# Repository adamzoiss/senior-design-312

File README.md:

# Senior Design Project - Team 312

**Share Point Quick Link:** [Project SharePoint](https://fsu-my.sharepoint.com/personal/amw21i_fsu_edu/_layouts/15/Doc.aspx?sourcedoc={c8d6e6cb-04f5-4a5c-a4a4-ac70581ecfba}&action=edit&wd=target%28Class%20Handouts.one%7C43749e4e-c570-4688-8d40-703e8b013bf2%2FSenior%20Design%20Projects%7C01b6a98f-3880-41ca-834b-d67c770890d6%2F%29&wdorigin=NavigationUrl)

---

**Table of Contents**

> _The links are clickable and will take you to that section or subsection._

- [**Operation Manual**](#operation-manual)

  - [How to start the device](#how-to-start-the-device)
  - [How to operate](#how-to-operate)

- [**Project Description**](#project-description)

  - [Overall Processes](#overall-processes)
  - [Audio Processing and Transmission](#audio-processing-and-transmission-of-data)
  - [Encryption/Decryption Information](#how-the-encryption-and-decryption-works)
  - [Materials](#materials)

- [**RPI Setup**](#rpi-setup)

  - [Flashing an OS](#flashing-an-os)
  - [How to SSH to rpi](#how-to-ssh-to-rpi)
  - [Driver Installation](#driver-installation)

- [**Coding Environment**](#coding-environment)

  - [Running the Code](#running-the-code)

- [**Creating a daemon**](#creating-a-daemon)

- [**Using Git**](#using-git)

  - [Setting up Git](#setting-up-git)
  - [Git usage](#git-usage)

- [**Documenting Python Code**](#documenting-python-code)

  - [Code Documentation](#code-documentation)
  - [Type Hinting Guide](#type-hinting-guide)

- [**Contributors**](#contributors)

**Resources:**

[KiCad](https://www.kicad.org/) - The circuit schematic and PCB design files are in the kicad folder.

[PEP 8 – Style Guide for Python Code](https://peps.python.org/pep-0008/#introduction) - Guideline for how to code in Python

[Python Project/Package Template](https://github.com/pypa/sampleproject) - To better understand the structure of the project, a template for python projects/packages can be viewed as a reference.

[Raspberry Pi pinout information](https://pinout.xyz/) - Useful for setting up buttons, switches, RF chip, etc. via the GPIO pins.

[Git Information](https://git-scm.com/book/en/v2) - Information on how to use git.

---

## Operation Manual:

A Guide on how to operate the end project will be discussed in this section.

### How to start the device:

Ideally a daemon could be used to start the program when booted up but there was a bug where the audio volume would only be set to 50%. The surefire way to get the device up and running is to first log in to the RPI5s and then configure it and and run the program manually:

```
alsamixer
```

- Set the volume to 100%

```
cd git/senior-design-312
penva
python src/managers/interface_manager.py
```

- This will start the program and show the logs in the terminal window

### How to operate

On the OLED screen there are two menus, Settings, and mode.

The Settings menu allows for the user to select and deselect the encryption for the device.

```
PENC - Packet Encryption: This is enables or disables the transceivers on board AES encryption.

DENC - Data Encryption: THis enables or disables the software encryption of the data.
```

In the Mode menu, the user can select the desired type of encryption for the data.

```
AES - Standard AES-256 Encryption

RSA - (NOT IMPLEMENTED) RSA Encryption

HYB - Hybrid Encryption method: RSA encrypted AES key
```

---

Volume Control

- The rotary encoder is used to change the onboard volume, which can be seen at the top left of the screen.

Selection of menu options

- The center button is used to select options in the menu.

Returning to the main menu

- The left button is used to return to the home screen.

Navigation

- The up and down buttons navigate through the menus.

Transmitting

- Pressing and holding the right button will start the transmission of the voice data from one device to the other. Releasing it will stop the transmission. Like a walkie-talkie, only one transceiver can be transmitting at a time.

---

## Project Description:

The purpose of the project is to have a hardware implementation for voice encryption. The approach taken was to use two Raspberry Pi 5's that are capable of encrypting and decrypting audio streams using AES or RSA. The encrypted stream is then sent to another Raspberry Pi via the RFM69 915MHz transceiver where it is then decrypted and played back. The functionality is like that of a rudimentary military grade radio (encrypted walkie talkie).

### Overall Processes:

To record the audio a button on the device is pressed, starting a thread to handle recording the audio and then transmitting it as shown in the diagram. The receiving device, upon receiving the RF signal and start sequence will start playing back the audio.

```mermaid
%%{init: {'theme': 'default', 'themeVariables': { 'fontSize': '18px', 'fontFamily': 'arial', 'edgeLabelBackground':'#ffffff'}, 'flowchart': {'diagramPadding': 40, 'curve': 'linear'}} }%%
flowchart LR
    %% Increase arrow thickness
    linkStyle default stroke-width:3px;

    subgraph sender["Audio Transmission"]
        record["Record Audio"] --> process["Process Audio"]
        process --> encode["Encode Audio"]
        encode --> encrypt["Encrypt Data"]
        encrypt --> send["Send Data"]
    end

    subgraph receiver["Reception and Playback"]
        receive["Receive Data"] --> decrypt["Decrypt Data"]
        decrypt --> decode["Decode Audio"]
        decode --> playback["Playback Audio"]
    end

    sender <==> receiver

    classDef default fill:#f0f8ff,stroke:#333,stroke-width:2px;
    classDef process fill:#e6ffe6,stroke:#333,stroke-width:2px;
    classDef encrypt fill:#ffe6e6,stroke:#333,stroke-width:2px;

    class record,process,encode,encrypt,send,receive,decrypt,decode,playback process;
```

### Audio Processing and Transmission of data:

[Diagrams and information](docs/design_flow_diagrams.md)

### How the encryption and decryption works:

This design used AES 256, RSA 4096, and a hybrid method that is outlined below:
[AES-256](docs/aes.md)
[RSA-4096](docs/rsa.md)

### Materials:

- [Raspberry Pi 5](https://www.adafruit.com/product/5813)
- [RPI UPS](https://www.amazon.com/Geekworm-X1200-Raspberry-Shutdown-Detection/dp/B0CRYVC8C5/ref=sr_1_5?crid=3T93BCIOWTPNQ&dib=eyJ2IjoiMSJ9.DSS9mwB54EGjoH9xGkIHFd17faf9UodmdVZNEF_NOwU1_TtXE9s5ghDnBO93wSyNeB1lbRl8e1wEuyPHb3ZzxMwYsCVhmp-j85LuohlRSUfx-YZh10-CHeAW6Z2ln4s2YudasiG1aBX-cWL1VihQCH_vzZzjAtUG9teGnXM9BbOQCqw_GdSpZU175fsOAMTuqZAPb5n3mfgUwXqlgPdfhwnoqzu5ng3niiaieRxPhM2FF5Hz5nVOXCaIMCLdwqQHWaklxH1ObAC3PyNYaox4awEBOQx2zcOAy6-PPfX7jiT5Lc-Iv-FmTJBIp-wI4evsTNgZJfQ-FAyS--bPdEAYpfdK69StwQNbdMvML9t9LII.ysi9Ba5JT9anmJP7jrCq64x9GX5JekWu3_toRT-0F-U&dib_tag=se&keywords=rpi5+ups+geekworm&qid=1743437047&s=electronics&sprefix=rpi5+ups+geekworm%2Celectronics%2C111&sr=1-5)
- [ANO Directional Navigation](https://www.adafruit.com/product/5001)
- [RFM69HCW Transceiver](https://www.adafruit.com/product/3070)
- [Voice Bonnet](https://www.adafruit.com/product/4757)
- [OLED Display](https://www.amazon.com/dp/B0CHF7LHVT?ref=ppx_yo2ov_dt_b_fed_asin_title&th=1)
- [Speaker](https://www.adafruit.com/product/4227)

---

## RPI Setup:

### Flashing an OS:

1. Download the [Raspberry PI imager](https://www.raspberrypi.com/software/)

2. Select RPI 5 as device and Raspian 64-bit Lite as OS
   2.1 - For all the drivers for this project, a non desktop version must be used.

3. Customize settings before flashing

   - Name the device (ex. rpi5-312)
   - Set username (ex. team312)
   - Set password (ex. password)
   - Enable SSH in second tab
   - Finally flash the SD card with the OS

4. Plug SD card in, power on

---

### How to SSH to rpi:

_This step is optional_

Using powershell or terminal (must be on same network)

```bash
ssh [username]@[device name].local
```

- Follow steps to allow connection

- To make life simpler going forward, get the VS code extension _Remote Explorer_
  - Then follow steps to make a SSH connection in VS code.

---

### Driver Installation:

- This will update all the base packages and drivers for the Raspberry Pi.

  ```bash
  sudo apt update
  sudo apt -y upgrade
  sudo reboot
  ```

  - The following steps are for ease of installation of all the necessary packages/drivers for the RPI. Running the setup script will install all the packages as well as create a virtual python environment in the _senior-design-312_ directory.

  - This script also adds aliases to the .bashrc and exports the directory of the project to PYTHONPATH.

  ADDED ALIASES:

  - ptree - shows the tree of the directory, excludes some of the unimportant files.
  - penvca - Creates and activates a python virtual environment in _**.env**_
  - penva - Activates the python virtual environment.

  ```bash
  sudo apt install -y git
  mkdir git
  cd git
  git clone https://github.com/adamzoiss/senior-design-312.git
  cd senior-design-312
  cd setup_utils
  chmod +x setup.sh
  ./setup.sh
  ```

  - After the reboot, change the directory to _senior-design-312_ and run:

    ```bash
    penva
    ```

  All of the code should now be ready to run in the project.

---

## Coding Environment:

- When running the code ensure that the virtual environment is activated, if the setup script was run, in the project directory, run:
  ```bash
  penva
  ```

---

### Running the Code:

- Assuming the setup script was run to configure the RPI, ensure the virtual environment is activated (.env) to the left of your bash info, and run:

  ```bash
  python "path to python program"
  ```

- To run the tests and view the statistics, run:
  ```bash
  pytest
  ```

---

## Creating a daemon:

A daemon is a background process that runs continuously and independently of user interaction. It starts at boot (or when needed) and runs in the background, typically without a graphical interface. Daemons are often used for tasks like logging, networking, and running services (like web servers, audio managers, etc.). In the case of this project, a daemon is used to start the interface manager program on boot, and if it crashes, restarts the program.

- Creating a Systemd Service:
  ```bash
  sudo nano /etc/systemd/system/run-py-program.service
  ```
  > This should be pasted and modified to use the correct python path, program directory, and _pi_ username

```
[Unit]
Description=My Python Script Daemon
After=network.target sound.target
Wants=pulseaudio.service

[Service]
ExecStart=/home/pi/git/senior-design-312/.env/bin/python /home/pi/git/senior-design-312/src/managers/interface_manager.py
WorkingDirectory=/home/adamzoiss/git/senior-design-312
Environment="PYTHONPATH=/home/pi/git/senior-design-312"
User=pi
Group=pi
Restart=always
RestartSec=5
StandardOutput=append:/home/pi/git/senior-design-312/logs/system.log
StandardError=append:/home/pi/git/senior-design-312/logs/system.err

[Install]
WantedBy=multi-user.target
```

- Allow Systemd to use pulse audio:

  > By default, PulseAudio does not allow system services to access it. Run:

  ```
  sudo nano /etc/pulse/client.conf
  ```

  - At the end of the file, add:
    ```
    autospawn = yes
    ```
  - Then restart pulseaudio
    ```
    pulseaudio -k
    pulseaudio --start
    ```

- Enabling and staring the daemon:

  > To apply the changes made in the _.service_ file:

  ```
  sudo systemctl daemon-reload
  ```

  > To enable:

  ```
  sudo systemctl enable run-py-program.service
  ```

  > To start:

  ```
  sudo systemctl start run-py-program.service
  ```

  > View the status:

  ```
  sudo systemctl status run-py-program.service
  ```

  - More useful commands:
    ```
    sudo systemctl disable run-py-program.service
    sudo systemctl stop run-py-program.service
    sudo systemctl restart run-py-program.service
    ```

---

## Using Git:

Git is a distributed version control system designed to track changes in source code during software development. It allows multiple developers to collaborate on a project by managing code changes, maintaining a history of modifications, and enabling branching and merging workflows. Git ensures code integrity and simplifies collaboration by providing tools to resolve conflicts and review changes.

### Setting up Git:

- First set username and password via:

  ```bash
  git config --global user.name "github username"
  git config --global user.email "github email"
  ```

  - To verify they were set correctly:
    ```bash
    git config --global -l
    ```

  1. Make a github account (Make sure you set your username and email in global config)
  2. install _gh_ for github authentication
     ```bash
     sudo apt install gh
     gh auth login
     ```
  3. Follow steps and log in
  4. Verify with:
     ```bash
     gh auth status
     ```

---

### Git usage

- Always make edits in a `branch`, do not work directly on main. To see what branch is active:

  ```bash
  git branch
  ```

- To `checkout` an active branch with name _branchname_:

  ```bash
  git checkout branchname
  ```

- To create a new working branch:

  ```bash
  git checkout -b nameofbranch
  ```

- After making changes on a branch, save (`commit`) the changes by:

  ```bash
  git commit -a -m "brief description of what was done"
  ```

  - This saves the changes locally on your computer, to add (push the changes to github)
    ```bash
    git push origin branchname
    ```
    - Alternatively, If you want Git to automatically set upstream branches when pushing new local branches, you can enable:
      ```bash
      git config --global push.autoSetupRemote true
      ```
      This way, next time you create a new branch and push, Git will automatically set up the remote tracking branch. The command will now look like:
      ```bash
      git push
      ```

- Getting the most up to date code:
  - save changes that were done on your branch via a commit or stash
  - check out `main`
    ```bash
    git fetch
    ```
    ```bash
    git pull
    ```
  - the most up to date version of main is now what you see

---

## Documenting Python Code:

### Code Documentation

`numpy` style documentation is being used for this project.

**Example of a NumPy-style docstring:**

```python
import numpy as np

def compute_mean(arr):
    """
    Compute the mean of a NumPy array.

    Parameters
    ----------
    arr : numpy.ndarray
        Input array of numerical values.

    Returns
    -------
    float
        The mean (average) of the input array.

    Raises
    ------
    ValueError
        If the input is not a NumPy array.

    Examples
    --------
    >>> import numpy as np
    >>> arr = np.array([1, 2, 3, 4, 5])
    >>> compute_mean(arr)
    3.0
    """
    if not isinstance(arr, np.ndarray):
        raise ValueError("Input must be a NumPy array.")
    return arr.mean()
```

**Breakdown of the NumPy docstring format:**

- Short summary: The first line briefly describes what the function does.
- Parameters: List of arguments, types, and descriptions.
- Returns: Description of the return value and type.
- Raises: Expected exceptions that may be thrown.
- Examples: Demonstrates usage with `doctest`-style examples.

---

**Class with NumPy-style Docstrings**

This class represents a **Simple Linear Regression** model.

```python
import numpy as np

class SimpleLinearRegression:
    """
    A simple linear regression model using the least squares method.

    Attributes
    ----------
    coef_ : float
        The slope (coefficient) of the regression line.
    intercept_ : float
        The y-intercept of the regression line.

    Methods
    -------
    fit(X, y)
        Fits the model to the data.
    predict(X)
        Predicts values using the trained model.
    """

    def __init__(self):
        """
        Initializes the SimpleLinearRegression model with no trained parameters.
        """
        self.coef_ = None
        self.intercept_ = None

    def fit(self, X, y):
        """
        Fit the linear regression model to the given dataset.

        Parameters
        ----------
        X : numpy.ndarray
            Feature array of shape (n_samples,).
        y : numpy.ndarray
            Target array of shape (n_samples,).

        Raises
        ------
        ValueError
            If `X` and `y` have different lengths.

        Examples
        --------
        >>> import numpy as np
        >>> X = np.array([1, 2, 3, 4, 5])
        >>> y = np.array([2, 4, 6, 8, 10])
        >>> model = SimpleLinearRegression()
        >>> model.fit(X, y)
        """
        if len(X) != len(y):
            raise ValueError("X and y must have the same length.")

        X_mean = np.mean(X)
        y_mean = np.mean(y)

        num = np.sum((X - X_mean) * (y - y_mean))
        den = np.sum((X - X_mean) ** 2)

        self.coef_ = num / den
        self.intercept_ = y_mean - self.coef_ * X_mean

    def predict(self, X):
        """
        Predict the target values for given input data.

        Parameters
        ----------
        X : numpy.ndarray
            Feature array of shape (n_samples,).

        Returns
        -------
        numpy.ndarray
            Predicted values based on the trained model.

        Raises
        ------
        ValueError
            If the model has not been trained yet.

        Examples
        --------
        >>> import numpy as np
        >>> X = np.array([6, 7, 8])
        >>> model = SimpleLinearRegression()
        >>> model.fit(np.array([1, 2, 3, 4, 5]), np.array([2, 4, 6, 8, 10]))
        >>> model.predict(X)
        array([12., 14., 16.])
        """
        if self.coef_ is None or self.intercept_ is None:
            raise ValueError("Model is not trained. Call `fit` first.")

        return self.coef_ * X + self.intercept_
```

**NumPy Docstrings Benefits**

- Structured and readable: Clearly defines parameters, return values, and exceptions.
- Works with auto-documentation tools like Sphinx.
- Encourages best practices: Makes it easier to maintain and understand code.

---

### Type Hinting Guide:

1. Function Arguments & Return Types

   ```python
   def add(x: int, y: int) -> int:
       return x + y
   ```

   `x: int` and `y: int` specify that x and y should be integers.

   `-> int` means the function returns an integer.

2. Variable Annotations

   ```python
   name: str = "Alice"
   age: int = 25
   height: float = 5.9
   is_active: bool = True
   ```

3. Lists, Tuples, and Dictionaries

   Use `list`, `tuple`, and `dict` with generic types:

   ```python
   from typing import List, Tuple, Dict

   numbers: List[int] = [1, 2, 3, 4]
   point: Tuple[float, float] = (3.5, 7.2)
   person: Dict[str, int] = {"age": 30, "score": 95}
   ```

- `List[int]`: A list of integers.
- `Tuple[float, float]`: A tuple with two floats.
- `Dict[str, int]`: A dictionary with string keys and integer values.

4. Optional & Union Types

   **Optional Type (Allows `None`)**

   ```python
   from typing import Optional

   def get_user_name(user_id: int) -> Optional[str]:
       return "Alice" if user_id == 1 else None
   ```

   `Optional[str]` is equivalent to `Union[str, None]`.

   **Union (Multiple Types Allowed)**

   ```python
   from typing import Union

   def parse_value(value: Union[int, str]) -> str:
       return str(value)
   ```

   `Union[int, str]` means `value` can be an **int** or **str**.

5. Custom Classes as Types

   ```python
   class User:
       def __init__(self, name: str):
           self.name = name

   def greet(user: User) -> str:
       return f"Hello, {user.name}!"
   ```

   The function `greet` expects a `User` instance.

6. Callable (Hinting Functions)

   ```python
   from typing import Callable

   def execute(func: Callable[[int, int], int], x: int, y: int) -> int:
       return func(x, y)

   def multiply(a: int, b: int) -> int:
       return a * b

   result = execute(multiply, 3, 4)  # Returns 12
   ```

   `Callable[[int, int], int]` means a function that:

   - Takes two integeres.
   - Returns an integer.

7. Type Aliases (For Readability)

   ```python
   from typing import List

   Coordinates = List[Tuple[float, float]]  # Type alias

   route: Coordinates = [(10.0, 20.0), (30.5, 40.2)]
   ```

   Now, `Coordinates` can be used instead of `List[Tuple[float, float]]`.

8. Type Variables (For Generic Functions & Classes)

   _This is the same concept in C++ as `template <Typename T>`_

   ```python
   from typing import TypeVar, Generic

   T = TypeVar('T')  # Generic Type

   def repeat(value: T, times: int) -> List[T]:
       return [value] * times

   print(repeat("Hello", 3))  # ['Hello', 'Hello', 'Hello']
   ```

   Here:

   - `T` is a Type Variable that allows any type.
   - `repeat` works with any type, maintaining type safety.

9. TypedDict (For Struct-like Dictionaries)

   ```python
   from typing import TypedDict

   class UserDict(TypedDict):
       name: str
       age: int

   user: UserDict = {"name": "Alice", "age": 30}
   ```

   This ensures `user` has only the specified keys and types.

10. `Self` Type Hinting for Methods

    Introduced in Python 3.11, `Self` hints that a method returns an instance of its class.

    ```python
    from typing import Self

    class Animal:
        def set_name(self, name: str) -> Self:
            self.name = name
            return self  # Returns instance for method chaining

    dog = Animal().set_name("Buddy")
    ```

---

**Static Type Checking with `mypy`**

To enforce type checking, install mypy:

```bash
pip install mypy
```

Then run:

```bash
mypy my_script.py
```

This will flag type errors before runtime.

---

## Contributors:

Danielle Awoniyi : danielle1.awoniyi@famu.edu

Amira McKaige : amm21bc@fsu.edu

Amelia Wondracek : amw21i@fsu.edu

Travis Gabauer : tg21b@fsu.edu

Adam Zoiss : aez18@fsu.edu

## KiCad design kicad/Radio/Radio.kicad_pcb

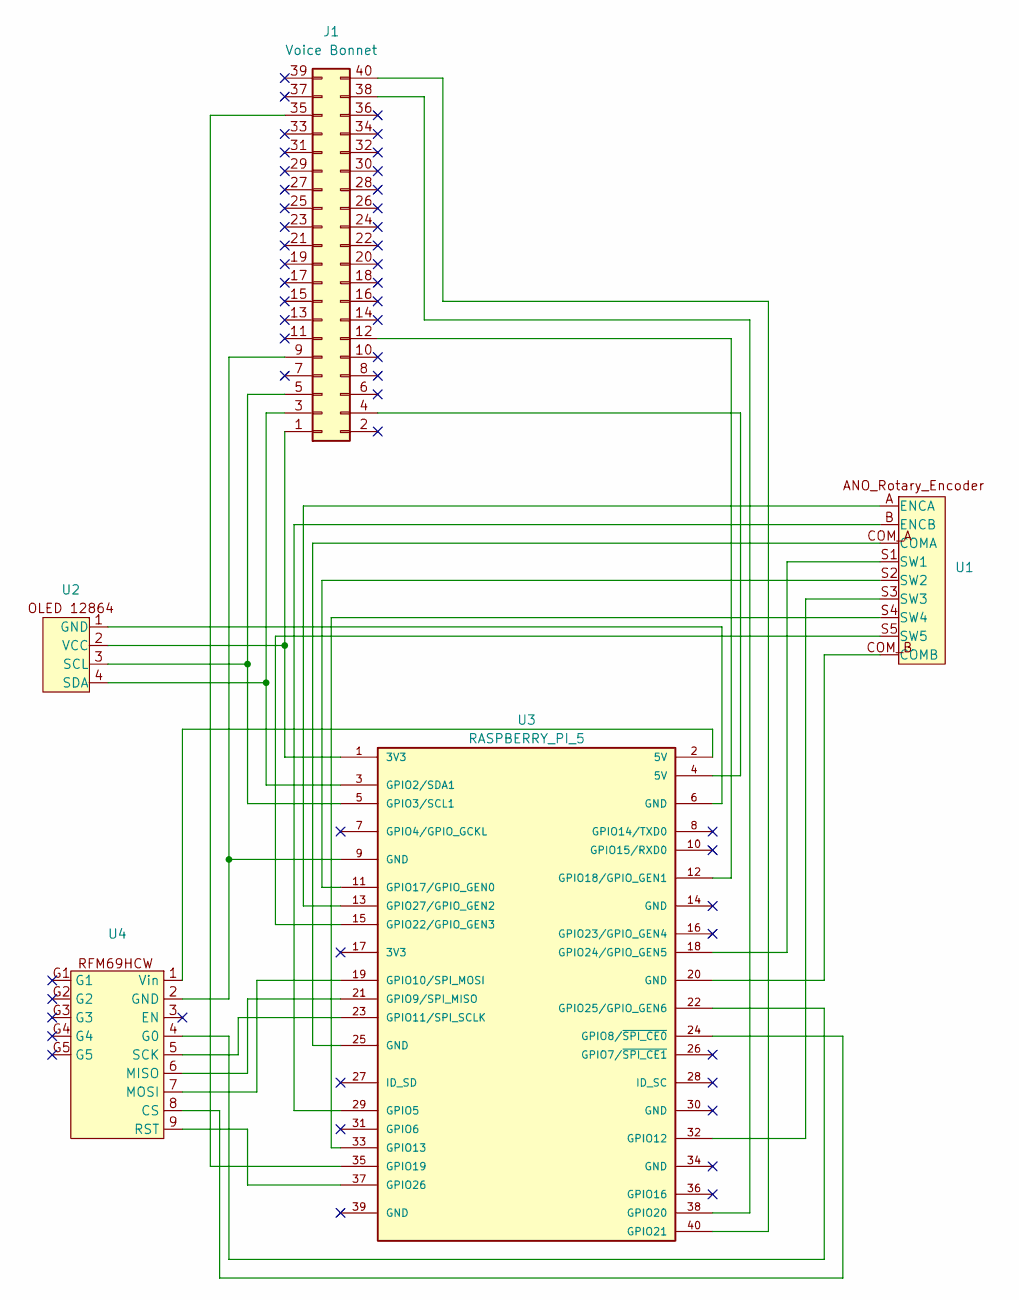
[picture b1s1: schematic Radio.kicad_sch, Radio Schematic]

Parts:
J1: Voice Bonnet; Voice_Bonnet
U1: ANO
U2: PinHeader_1x04_P2.54mm_Vertical
U3: RASPBERRY_PI_5; MODULE_RASPBERRY_PI_4B_4GB; PARTREV 4
U4: rfm69

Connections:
unnamed: J1.1, U2.2 (VCC), U3.1 (3V3)
unnamed: J1.3, U2.4 (SDA), U3.3 (GPIO2/SDA1)
unnamed: J1.4, U3.4 (5V)
unnamed: J1.5, U2.3 (SCL), U3.5 (GPIO3/SCL1)
unnamed: J1.9, U3.9 (GND), U4.2 (GND)
unnamed: J1.12, U3.12 (GPIO18/GPIO_GEN1)
unnamed: J1.35, U3.35 (GPIO19)
unnamed: J1.38, U3.38 (GPIO20)
unnamed: J1.40, U3.40 (GPIO21)
unnamed: U1.COM_A (COMA), U3.25 (GND)
unnamed: U1.COM_B (COMB), U3.20 (GND)
unnamed: U1.A (ENCA), U3.13 (GPIO27/GPIO_GEN2)
unnamed: U1.B (ENCB), U3.29 (GPIO5)
unnamed: U1.S1 (SW1), U3.18 (GPIO24/GPIO_GEN5)
unnamed: U1.S2 (SW2), U3.11 (GPIO17/GPIO_GEN0)
unnamed: U1.S3 (SW3), U3.32 (GPIO12)
unnamed: U1.S4 (SW4), U3.33 (GPIO13)
unnamed: U1.S5 (SW5), U3.15 (GPIO22/GPIO_GEN3)
unnamed: U2.1 (GND), U3.6 (GND)
unnamed: U3.24 (GPIO8/~SPI_CE0), U4.8 (CS)
unnamed: U3.21 (GPIO9/SPI_MISO), U4.6 (MISO)
unnamed: U3.19 (GPIO10/SPI_MOSI), U4.7 (MOSI)
unnamed: U3.23 (GPIO11/SPI_SCLK), U4.5 (SCK)
unnamed: U3.22 (GPIO25/GPIO_GEN6), U4.4 (G0)
unnamed: U3.37 (GPIO26), U4.9 (RST)
unnamed: U3.2 (5V), U4.1 (Vin)

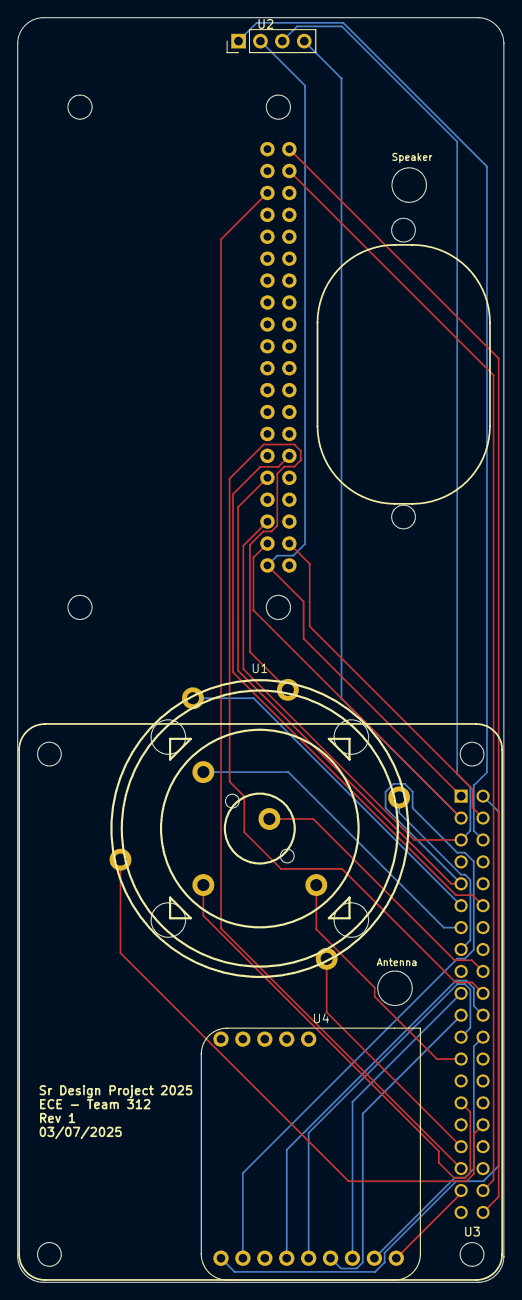
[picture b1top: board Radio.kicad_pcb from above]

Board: 2 copper layers, 56.4 x 146.6 mm, 5 parts (1 on the bottom side), 26 nets.

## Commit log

2025-01-14 Updated readme file
2025-01-14 Updated readme file part 2
2025-01-27 Create file structure
2025-01-27 added main file
2025-01-27 Working audio and encryption
2025-01-27 Updated encyption/decryption and audio driver
2025-02-01 Updated readme for hardware setup.
2025-02-02 Restructured repo to follow package guidelines. Added to readme.
2025-02-02 Added comments for init files.
2025-02-02 Added comments for init files part 2.
2025-02-02 more readme updates.
2025-02-06 Update readme to include documentation info.
2025-02-06 Small edits.
2025-02-11 added checking for monitoring in recording functions
2025-02-12 These are test files for RSA and a hybrid RSA and AES
2025-02-12 added keys for rsa
2025-02-12 added files
2025-02-12 Updated nonhybridRSA
2025-02-13 Change file destinations for rsa testing, fixes to readme and handlers.
2025-02-13 TX working on nrf24
2025-02-17 Working display and interface managers, need to combine them.
2025-02-17 Working mode selection from menu.
2025-02-18 Cleaned up new code structure
2025-02-18 Working proof of concept with sw5 and monitoring
2025-02-18 Clean up inheritance for gpio interface.
2025-02-18 exclude diff.txt
2025-02-21 Update pyproject.toml
    names added to authors list, names added to maintainers list, and dependencies list was updated
    -DD
2025-02-21 Update pyproject.toml
    corrected syntax errors in authors, maintainers, and dependencies
    -DD
2025-02-21 Update pyproject.toml
    dependencies listed line-by-line as recommended by Python
    -DD
2025-02-21 Update pyproject.toml
    pylance, pyarrow, wave added to dependencies
    -DD
2025-02-24 Testing interface setup.
2025-02-24 Added logging, volume support, daemon guide - TODO: Documentation
2025-02-24 Updated rsa with pyaudio
2025-02-24 Update pyproject.toml
    added dependencies
    -DD
2025-02-24 Updated channel and libraries
2025-02-24 Updated the audio_manager and crypto_manager with RSA code
2025-02-24 Fixed an issue to make sure that RSA and AES have seperate file names for the audio input
2025-02-25 Hybrid RSA and AES Implementation, there's an added part to hear the noise to make sure everything is being encrypted right
2025-02-26 Added a key_creator to make the hybrid keys
2025-02-26 Added key_creator
2025-02-26 updated the git ignore
2025-02-26 Removing old created keys
2025-02-26 Fixed an issue with loading the keys
2025-02-28 Update SSD1306_display.py
    type hint for class and functions
    -DD
2025-02-28 Update base_screen.py
    type hint for class and funcs
    -DD
2025-02-28 Update screens.py
    type hint classes and funcs
    -DD
2025-02-28 Working voice bonnet, speaker, mic, controls, and screen
2025-02-28 Merged changes into main, made corrections, resolved conflicts.
2025-02-28 Adding automatic integration testing.
    Added simple unit tests for the crypto and audio managers and documented the yaml file.
2025-03-01 Added thread manager, cleaned up some of the code, added debug screen & functionality.
2025-03-03 Ported adafruit rfm69hcw code to be used on rpi and example to receive based on interrupts.
2025-03-03 added function to check for USB devices and pull key files from it
2025-03-03 added error checking to stop process if files aren't found
2025-03-03 added comments, removed unneccessary libraries added before
2025-03-03 added comments, removed libraries
2025-03-04 Taking a step back for now to reorganize some code.
2025-03-04 Restructured
2025-03-06 Add rf_manager, need to add logging and docs.
2025-03-06 Ported transceiver class, integrated radio functionality.
2025-03-06 Changed file name for all the constants to be more clear.
2025-03-08 Added opuslib as a dependency.
2025-03-16 Update crypto_manager.py
    type hint on data in def encrypt and def decrypt
    -DD
2025-03-16 Update display.py
    type hint data in def write_data
    -DD
2025-03-23 Fixed contants, adjusted volume init.
2025-03-23 Add audio stream unit test and mocking, separated audio manager to have a base.
2025-03-25 creating a setup script.
2025-03-25 updates to setup.
2025-03-25 updates again.
2025-03-25 setup script
2025-03-25 Add logs directory, added some code to the setup.
2025-03-25 Fixed setup script.
2025-03-25 Updates.
2025-03-26 Aded simple test for TX and RX.
2025-03-27 Added a docs folder and cleaned up a little bit of the code.
2025-03-28 added conditions and file for speed and decryption success testing
2025-03-28 added test file
2025-03-30 Added setup script, fixed bugs, added UI to disable encryption, added audio processing, updated docs.
2025-03-31 Added testing framework, added encryption options in settings ui tab. Updated docs.
2025-03-31 Updated function passing of arguments for encryption in settings menu.
2025-03-31 Update volume indicator position.
2025-03-31 readme fix.
2025-03-31 Finished readme fixes.
2025-04-01 fixed path to the file used for testing, used perf_counter for more accurate time measurement
2025-04-02 Update Frequency of transceiver.
2025-04-03 Integrating the RSA, AES, and hybrid
2025-04-03 integration of algorithms
2025-04-03 Edit to key_creator.py to handle if there is no usb
2025-04-03 Edit to key_creator.py to handle making hybrid keys
2025-04-03 Edit to key_creator.py to handle making hybrid keys edit2
2025-04-03 Edit to key_creator.py to handle making hybrid keys edit3
2025-04-03 Edit to key_creator.py to handle making hybrid keys edit4
2025-04-04 Added more docs, updated readme, added interface for encryption mode.
2025-04-04 Fixed UI handling inputs
2025-04-04 UI hotfix.
2025-04-04 Fix to support operation with monitor.
2025-04-06 added encoding and decoding tests to test_base_audio_manager
2025-04-06 added key_creator file from the testRSA branch (still need to change it to work on linux)
2025-04-07 Make charts more readable.
2025-04-07 All diag updates.
2025-04-07 Fixed graphs.
2025-04-08 Audio device testing.
2025-04-08 Removed unneeded code.
2025-04-08 Integrated hybrid encryption.
2025-04-08 Fixed bug where mode not shown if backed out of mode menu.
2025-04-08 Update to remove bug if rsa is chosen.
2025-04-08 Fixed typo.
2025-04-08 Added executable to set the alsamixer to max.
2025-04-08 testing path config
2025-04-16 Added more to the readme and added the kicad files.
